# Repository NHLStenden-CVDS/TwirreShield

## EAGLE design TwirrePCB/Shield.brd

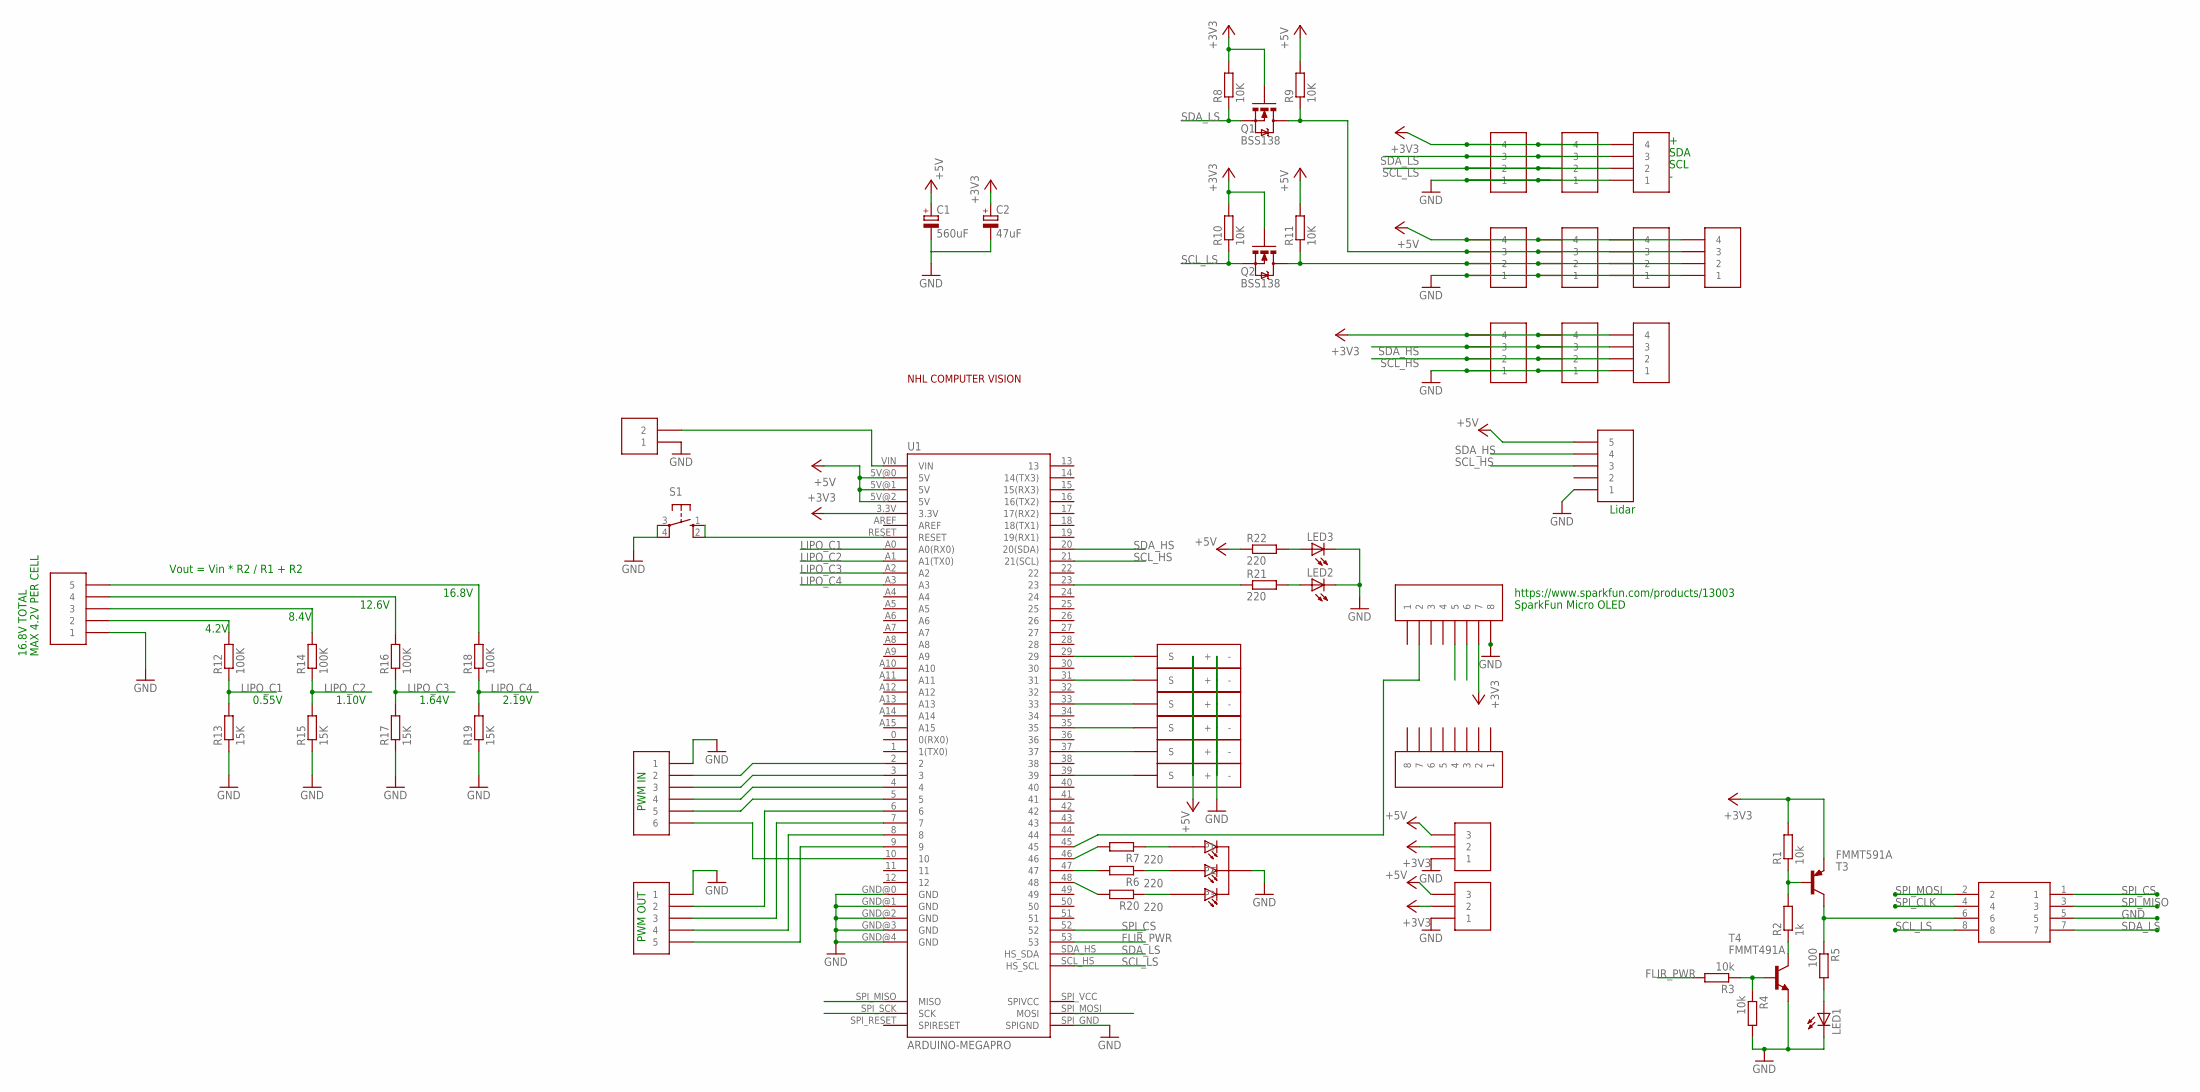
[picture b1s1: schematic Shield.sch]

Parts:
C1: 560uF; 153CLV-1010
C2: 47uF; 153CLV-0605
LED1, LED2, LED3: LEDSML0805; SML0805
Q1, Q2: BSS138; SOT23-3
R1, R3, R4: 10k; R0805
R2: 1k; R0805
R5: 100; R0805
R6, R7, R20, R21, R22: 220; R0805
R8, R9, R10, R11: 10K; R0805
R12, R14, R16, R18: 100K; R0805
R13, R15, R17, R19: 15K; R0805
S1: 10-XX; B3F-10XX
T3: FMMT591A; SOT23-BCE
T4: FMMT491A; SOT23-BEC
U1: ARDUINO-MEGAPRO; ARDUINO_MEGA-PRO-3.3V
U$1: RGB5MMRGB5MM; RGB5MM
U$2, U$3, U$4, U$5, U$6, U$7, U$8, U$9, U$10, U$11: JST-4
U$12, U$13: LIDAR; JST-5
U$14, U$15: JST-3
U$16: JST-2
U$17: JST-6
U$18: JST-5
U$19, U$20, U$21, U$22, U$23, U$24: SERVOHEADER
U$25: IDC-8WAY
U$26, U$27: OLEDHEADER
U$28: NHLLOGO

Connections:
+3V3: C2.+, Q1.1 (G), Q2.1 (G), R1.2, R8.2, R10.2, T3.E, U1.3.3V, U$2.4, U$3.4, U$4.4, U$8.4, U$9.4, U$10.4, U$14.2, U$15.2, U$26.P$7 (7)
+5V: C1.+, R9.2, R11.2, R22.1, U1.5V@0 (5V), U1.5V@1 (5V), U1.5V@2 (5V), U$5.4, U$6.4, U$7.4, U$11.4, U$12.5, U$14.3, U$15.3, U$19.+, U$20.+, U$21.+, U$22.+, U$23.+, U$24.+
FLIR_PWR: R3.2, U1.53
GND: C1.-, C2.-, LED1.C, LED2.C, LED3.C, R4.2, R13.1, R15.1, R17.1, R19.1, S1.3, S1.4 (P1), T4.E, U1.GND@0 (GND), U1.GND@1 (GND), U1.GND@2 (GND), U1.GND@3 (GND), U1.GND@4 (GND), U1.SPI_GND (SPIGND), U$1.C, U$2.1, U$3.1, U$4.1, U$5.1, U$6.1, U$7.1, U$8.1, U$9.1, U$10.1, U$11.1, U$12.1, U$13.1, U$14.1, U$15.1, U$16.1, U$17.1, U$18.1, U$19.-, U$20.-, U$21.-, U$22.-, U$23.-, U$24.-, U$25.5, U$26.P$8 (8)
LIPO_C1: R12.1, R13.2, U1.A0 (A0(RX0))
LIPO_C2: R14.1, R15.2, U1.A1 (A1(TX0))
LIPO_C3: R16.1, R17.2, U1.A2
LIPO_C4: R18.1, R19.2, U1.A3
unnamed: R1.1, R2.2, T3.B
unnamed: R2.1, T4.C
unnamed: R3.1, R4.1, T4.B
unnamed: LED1.A, R5.2
unnamed: U1.5, U$17.5
unnamed: U1.4, U$17.4
unnamed: R12.2, U$13.2
unnamed: U1.3, U$17.3
unnamed: U1.2, U$17.2
unnamed: R14.2, U$13.3
unnamed: R16.2, U$13.4
unnamed: R18.2, U$13.5
unnamed: U1.10, U$17.6
unnamed: R20.2, U1.48
unnamed: R6.2, U1.47
unnamed: U1.6, U$18.2
unnamed: U1.7, U$18.3
unnamed: U1.8, U$18.4
unnamed: U1.9, U$18.5
unnamed: R7.2, U1.46
unnamed: R20.1, U$1.P3
unnamed: R6.1, U$1.P2
unnamed: R7.1, U$1.P1
unnamed: U1.45, U$26.P$2 (2)
unnamed: U1.35, U$21.S
unnamed: U1.33, U$22.S
unnamed: U1.31, U$23.S
unnamed: U1.39, U$19.S
unnamed: U1.37, U$20.S
unnamed: LED2.A, R21.2
unnamed: R21.1, U1.23
unnamed: LED3.A, R22.2
unnamed: S1.1 (S), S1.2 (S1), U1.RESET
unnamed: U1.VIN, U$16.2
unnamed: U1.29, U$24.S
SCL_HS: U1.21 (21(SCL)), U$8.2, U$9.2, U$10.2, U$12.3
SCL_LS: Q2.2 (S), R10.1, U1.SCL_HS (HS_SCL), U$2.2, U$3.2, U$4.2, U$25.8, U$26.P$5 (5)
SCL_LS_5: Q2.3 (D), R11.1, U$5.2, U$6.2, U$7.2, U$11.2
SDA_HS: U1.20 (20(SDA)), U$8.3, U$9.3, U$10.3, U$12.4
SDA_LS: Q1.2 (S), R8.1, U1.SDA_HS (HS_SDA), U$2.3, U$3.3, U$4.3, U$25.7, U$26.P$6 (6)
SDA_LS_5: Q1.3 (D), R9.1, U$5.3, U$6.3, U$7.3, U$11.3
SPI_CLK: U1.SPI_SCK (SCK), U$25.4
SPI_CS: U1.52, U$25.1
SPI_MISO: U1.SPI_MISO (MISO), U$25.3
SPI_MOSI: U1.SPI_MOSI (MOSI), U$25.2
SPI_VIN: R5.1, T3.C, U$25.6

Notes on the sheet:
SDA
SCL
MAX 4.2V PER CELL
16.8V TOTAL
4.2V
8.4V
12.6V
16.8V
Vout = Vin * R2 / R1 + R2
0.55V
1.10V
1.64V
2.19V
Lidar
PWM IN
PWM OUT
https://www.sparkfun.com/products/13003
SparkFun Micro OLED

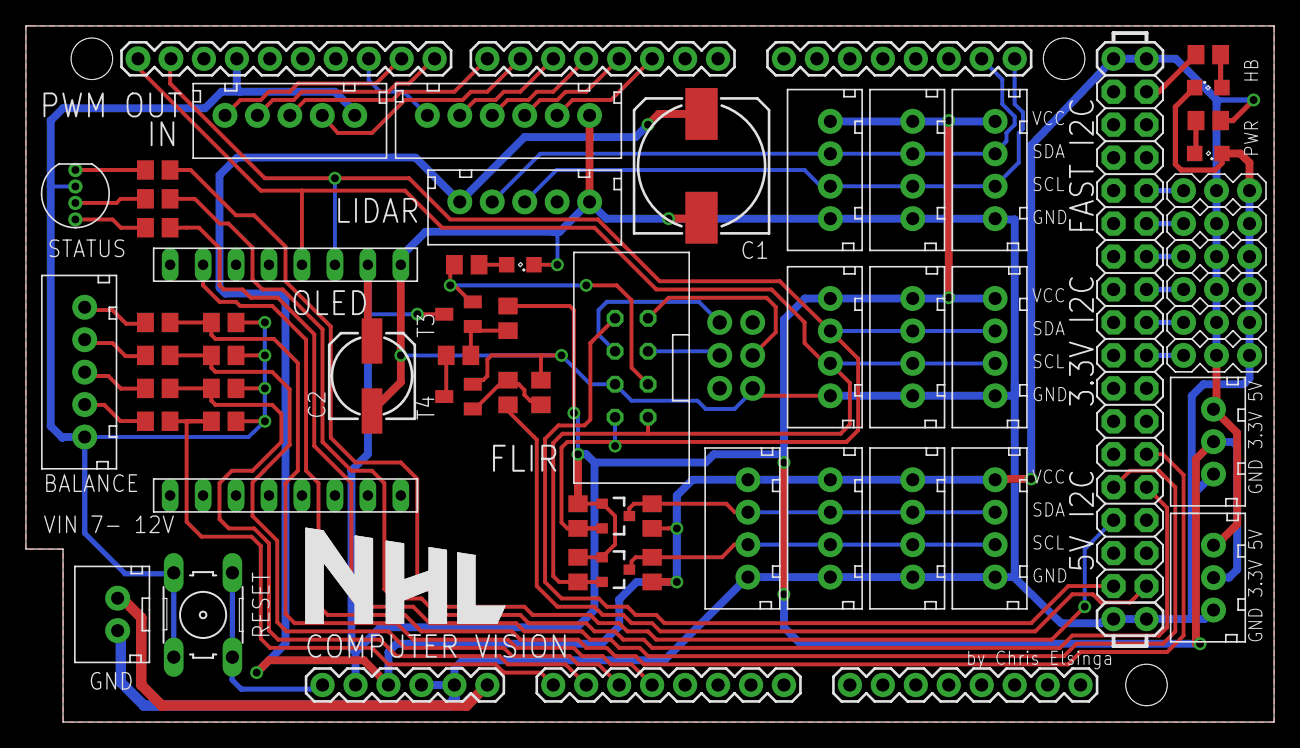
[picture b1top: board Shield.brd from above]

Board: 2 copper layers, 96.2 x 53.6 mm, 61 parts (0 on the bottom side), 54 nets.

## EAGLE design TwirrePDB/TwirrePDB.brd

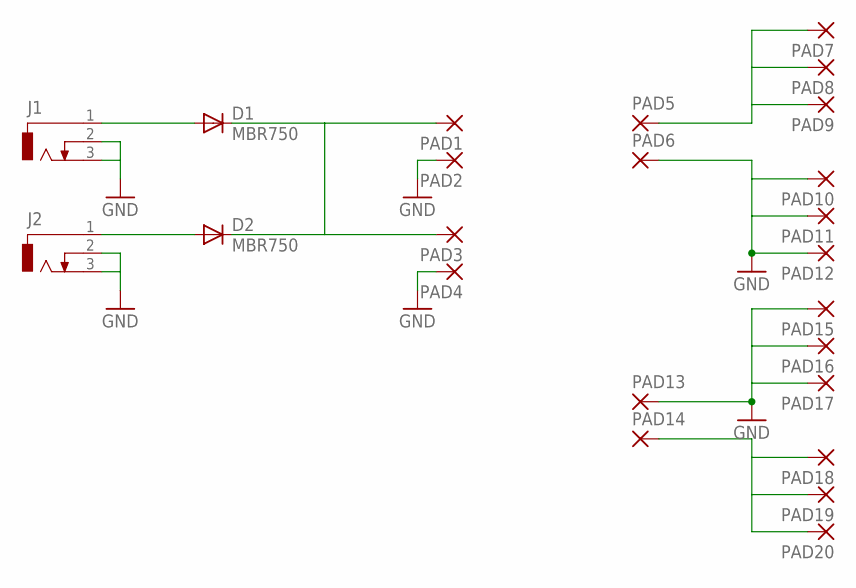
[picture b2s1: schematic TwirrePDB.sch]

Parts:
D1, D2: MBR750; TO220AC
J1, J2: DCJ0303
PAD1, PAD2, PAD3, PAD4, PAD5, PAD6, PAD7, PAD8, PAD9, PAD10, PAD11, PAD12, PAD13, PAD14, PAD15, PAD16, PAD17, PAD18, PAD19, PAD20: 2,54/0,9

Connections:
5V: PAD14.1, PAD18.1, PAD19.1, PAD20.1
12V: PAD5.1, PAD7.1, PAD8.1, PAD9.1
COMB: D1.C, D2.C, PAD1.1, PAD3.1
GND: J1.2, J1.3, J2.2, J2.3, PAD2.1, PAD4.1, PAD6.1, PAD10.1, PAD11.1, PAD12.1, PAD13.1, PAD15.1, PAD16.1, PAD17.1
unnamed: D2.A, J2.1
unnamed: D1.A, J1.1

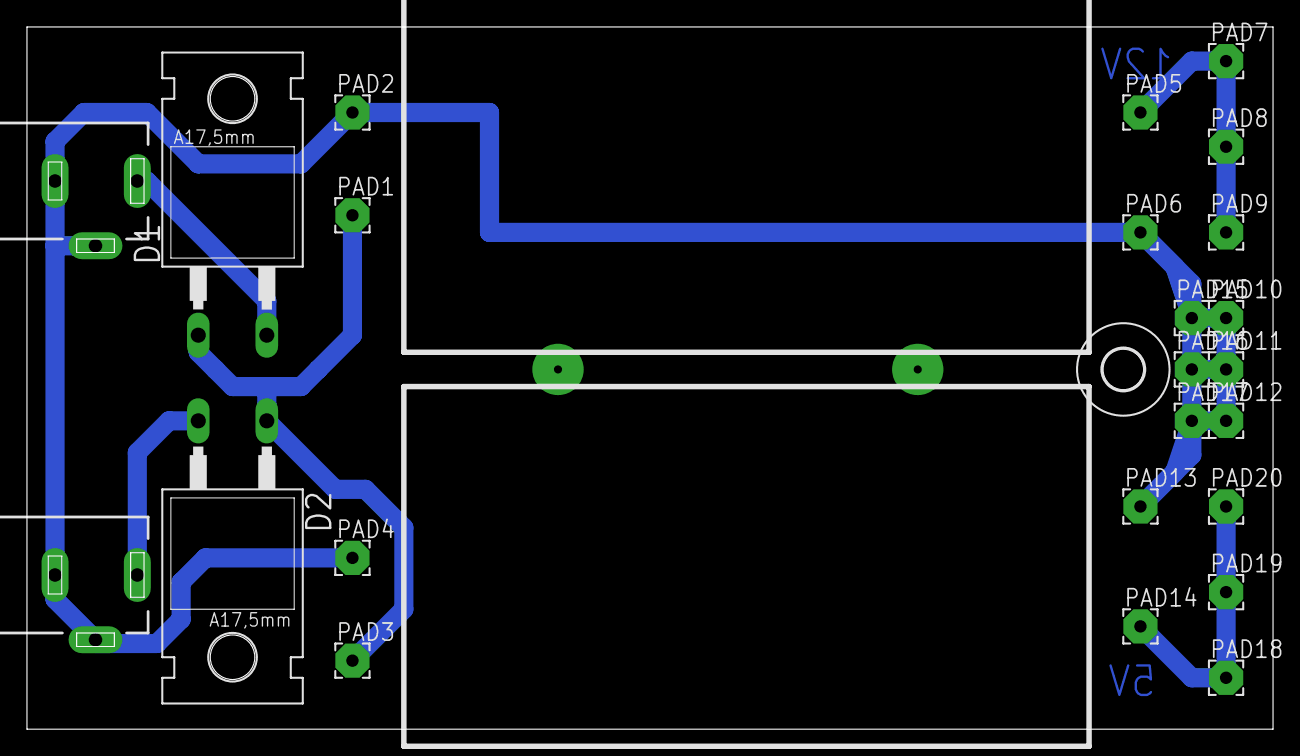
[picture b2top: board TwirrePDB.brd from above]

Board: 2 copper layers, 92.4 x 52.1 mm, 25 parts (0 on the bottom side), 6 nets.

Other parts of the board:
U$1: 3,0

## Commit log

2015-09-28 Add Arduino Due/Mega shield library
2015-09-28 Add Fast I2C Pins to library
2015-09-28 Basic schematic
2015-09-30 Add various components to library
2015-09-30 Modify LED part & Add more JST connectors
2015-09-30 Add caps and lots of other stuff
2015-09-30 Add IDC 8 way connector
2015-10-01 Move some parts and wires around, finished first revision
2015-10-06 Add Power Distribution Board
2015-10-06 Minor trace modifications
2015-10-12 Increase LED Resistor values
2015-10-14 Change Transistors for FMMT491A and FMMT591A
2015-10-15 Modify OLED and Servo Headers
2015-10-15 Add NHL Computer Vision logo
2015-11-06 Increase JST Hole size
2017-02-13 Add Credits
2018-05-25 Create LICENSE
2018-05-25 add partlist

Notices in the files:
parts and their libraries:
Arduino-Boards: Licensing: Creative Commons ShareAlike 4.0 International - https://creativecommons.org/licenses/by-sa/4.0
